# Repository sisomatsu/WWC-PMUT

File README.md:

# WWC-PMUT
Wearable, Wireless, and Compact PMUTs

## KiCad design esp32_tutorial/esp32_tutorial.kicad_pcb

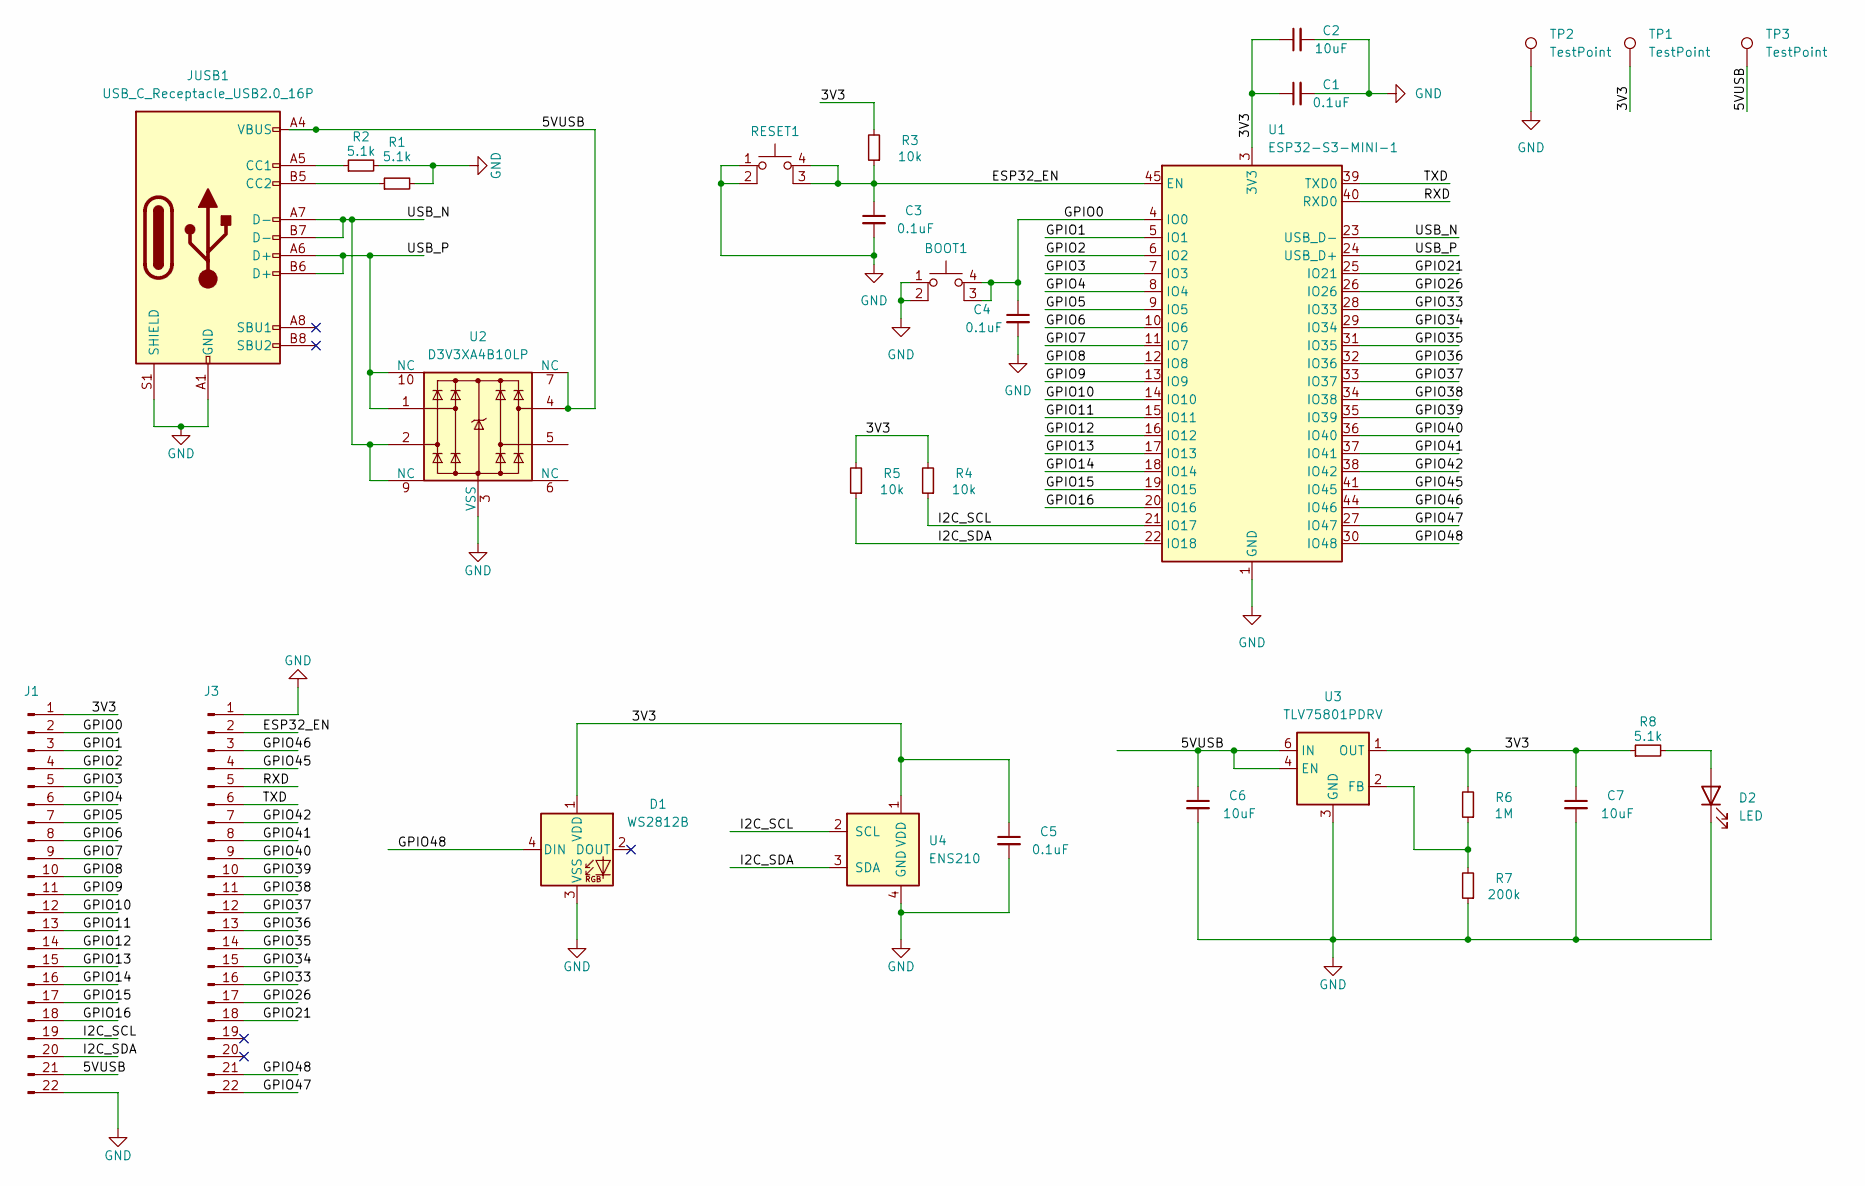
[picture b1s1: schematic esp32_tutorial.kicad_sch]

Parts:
BOOT1: SW_SPST_PTS810
C1, C3, C4, C5: 0.1uF; C_0603_1608Metric
C2, C6, C7: 10uF; C_0603_1608Metric
D1: WS2812B; LED_WS2812B_PLCC4_5.0x5.0mm_P3.2mm
D2: LED; LED_0603_1608Metric
J1, J3: PinHeader_1x22_P2.54mm_Vertical
JUSB1: USB_C_Receptacle_USB2.0_16P; USB_C_Receptacle_GCT_USB4105-xx-A_16P_TopMnt_Horizontal
R1, R2, R8: 5.1k; R_0603_1608Metric
R3, R4, R5: 10k; R_0603_1608Metric
R6: 1M; R_0603_1608Metric
R7: 200k; R_0603_1608Metric
RESET1: SW_SPST_PTS810
TP1, TP2, TP3: TestPoint; TP420X150
U1: ESP32-S3-MINI-1; ESP32-S2-MINI-1
U2: D3V3XA4B10LP; Diodes_UDFN-10_1.0x2.5mm_P0.5mm
U3: TLV75801PDRV; WSON-6-1EP_2x2mm_P0.65mm_EP1x1.6mm
U4: ENS210; AMS_QFN-4-1EP_2x2mm_P0.95mm_EP0.7x1.6mm

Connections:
/3V3: C1.1, C2.1, C5.1, C7.1, D1.1 (VDD), J1.1, R3.2, R4.2, R5.2, R6.2, R8.1, TP1.1, U1.3 (3V3), U3.1 (OUT), U4.1 (VDD)
/5VUSB: C6.1, J1.21, JUSB1.A4 (VBUS), JUSB1.A9 (VBUS), JUSB1.B4 (VBUS), JUSB1.B9 (VBUS), TP3.1, U2.4, U2.7 (NC), U3.4 (EN), U3.6 (IN)
/ESP32_EN: C3.1, J3.2, R3.1, RESET1.3 (K), RESET1.4 (A), U1.45 (EN)
/GPIO0: BOOT1.3 (K), BOOT1.4 (A), C4.1, J1.2, U1.4 (IO0)
/GPIO1: J1.3, U1.5 (IO1)
/GPIO2: J1.4, U1.6 (IO2)
/GPIO3: J1.5, U1.7 (IO3)
/GPIO4: J1.6, U1.8 (IO4)
/GPIO5: J1.7, U1.9 (IO5)
/GPIO6: J1.8, U1.10 (IO6)
/GPIO7: J1.9, U1.11 (IO7)
/GPIO8: J1.10, U1.12 (IO8)
/GPIO9: J1.11, U1.13 (IO9)
/GPIO10: J1.12, U1.14 (IO10)
/GPIO11: J1.13, U1.15 (IO11)
/GPIO12: J1.14, U1.16 (IO12)
/GPIO13: J1.15, U1.17 (IO13)
/GPIO14: J1.16, U1.18 (IO14)
/GPIO15: J1.17, U1.19 (IO15)
/GPIO16: J1.18, U1.20 (IO16)
/GPIO21: J3.18, U1.25 (IO21)
/GPIO26: J3.17, U1.26 (IO26)
/GPIO33: J3.16, U1.28 (IO33)
/GPIO34: J3.15, U1.29 (IO34)
/GPIO35: J3.14, U1.31 (IO35)
/GPIO36: J3.13, U1.32 (IO36)
/GPIO37: J3.12, U1.33 (IO37)
/GPIO38: J3.11, U1.34 (IO38)
/GPIO39: J3.10, U1.35 (IO39)
/GPIO40: J3.9, U1.36 (IO40)
/GPIO41: J3.8, U1.37 (IO41)
/GPIO42: J3.7, U1.38 (IO42)
/GPIO45: J3.4, U1.41 (IO45)
/GPIO46: J3.3, U1.44 (IO46)
/GPIO47: J3.22, U1.27 (IO47)
/GPIO48: D1.4 (DIN), J3.21, U1.30 (IO48)
/I2C_SCL: J1.19, R4.1, U1.21 (IO17), U4.2 (SCL)
/I2C_SDA: J1.20, R5.1, U1.22 (IO18), U4.3 (SDA)
/RXD: J3.5, U1.40 (RXD0)
/TXD: J3.6, U1.39 (TXD0)
/USB_N: JUSB1.A7 (D-), JUSB1.B7 (D-), U1.23 (USB_D-), U2.2, U2.9 (NC)
/USB_P: JUSB1.A6 (D+), JUSB1.B6 (D+), U1.24 (USB_D+), U2.1, U2.10 (NC)
GND: BOOT1.1, BOOT1.2, C1.2, C2.2, C3.2, C4.2, C5.2, C6.2, C7.2, D1.3 (VSS), D2.1 (K), J1.22, J3.1, JUSB1.A1 (GND), JUSB1.A12 (GND), JUSB1.B1 (GND), JUSB1.B12 (GND), JUSB1.S1 (SHIELD), R1.2, R2.2, R7.1, RESET1.1, RESET1.2, TP2.1, U1.1 (GND), U1.2 (GND), U1.42 (GND), U1.43 (GND), U1.46 (GND), U1.47 (GND), U1.48 (GND), U1.49 (GND), U1.50 (GND), U1.51 (GND), U1.52 (GND), U1.53 (GND), U1.54 (GND), U1.55 (GND), U1.56 (GND), U1.57 (GND), U1.58 (GND), U1.59 (GND), U1.60 (GND), U1.61 (GND), U1.62 (GND), U1.63 (GND), U1.64 (GND), U1.65 (GND), U2.3 (VSS), U2.8 (VSS), U3.3 (GND), U3.7 (GND), U4.4 (GND), U4.5 (GND)
unnamed: D2.2 (A), R8.2
unnamed: JUSB1.A5 (CC1), R2.1
unnamed: JUSB1.B5 (CC2), R1.1
unnamed: R6.1, R7.2, U3.2 (FB)

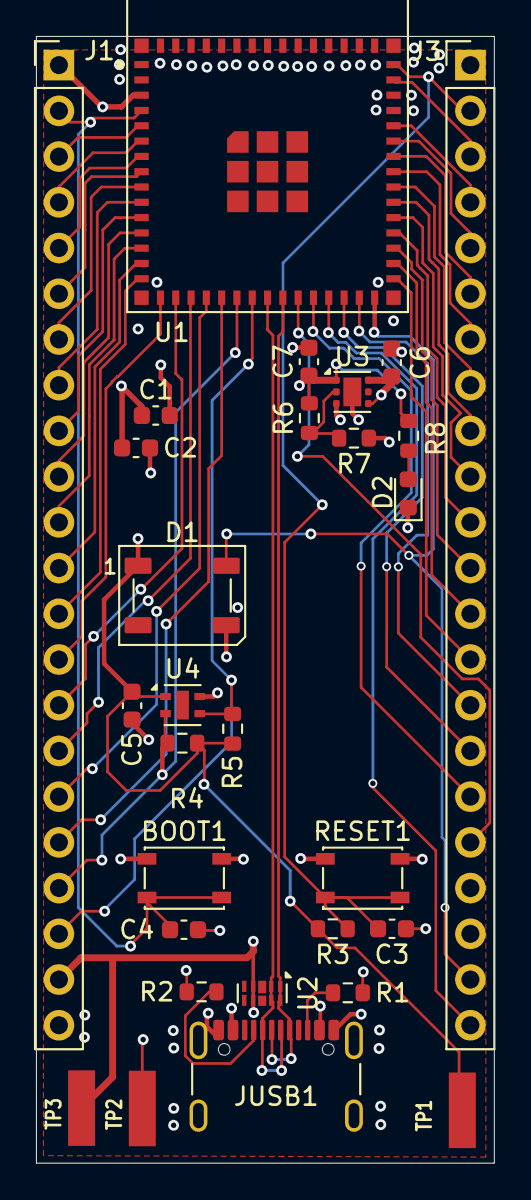
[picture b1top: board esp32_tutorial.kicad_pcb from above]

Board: 4 copper layers, 25.4 x 62.6 mm, 29 parts (0 on the bottom side), 47 nets.

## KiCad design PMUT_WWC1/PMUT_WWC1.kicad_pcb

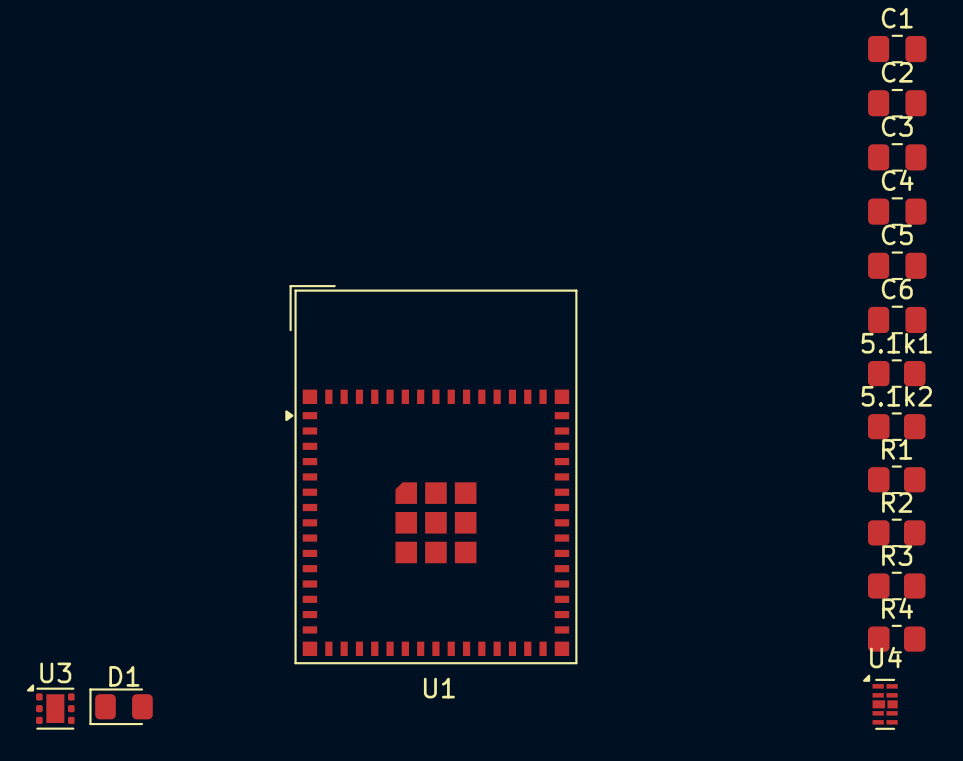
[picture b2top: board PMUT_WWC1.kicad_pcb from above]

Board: 2 copper layers, 16 parts (0 on the bottom side), 9 nets, no tracks yet.

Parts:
5.1k1, 5.1k2: R; R_0805_2012Metric_Pad1.20x1.40mm_HandSolder
C1, C3, C4: 0.1uF; C_0805_2012Metric_Pad1.18x1.45mm_HandSolder
C2, C5, C6: 10uF; C_0805_2012Metric_Pad1.18x1.45mm_HandSolder
D1: LED; D_0805_2012Metric_Pad1.15x1.40mm_HandSolder
R1: 10k; R_0805_2012Metric_Pad1.20x1.40mm_HandSolder
R2: 1M; R_0805_2012Metric_Pad1.20x1.40mm_HandSolder
R3: 200k; R_0805_2012Metric_Pad1.20x1.40mm_HandSolder
R4: 5.1k; R_0805_2012Metric_Pad1.20x1.40mm_HandSolder
U1: ESP32-S3-MINI-1; ESP32-S2-MINI-1
U3: TLV75801PDRV; WSON-6-1EP_2x2mm_P0.65mm_EP1x1.6mm
U4: D3V3XA4B10LP; Diodes_UDFN-10_1.0x2.5mm_P0.5mm

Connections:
/3V3: C1.1, C2.1, C6.1, R1.1, R2.1, R4.1, U1.3 (3V3), U3.1 (OUT)
/5VUSB: C5.1, U3.4 (EN), U3.6 (IN), U4.4, U4.7 (NC)
/GPIO0: C4.1, U1.4 (IO0)
/USB_N: U1.23 (USB_D-), U4.1, U4.10 (NC)
/USB_P: U1.24 (USB_D+), U4.2, U4.9 (NC)
GND: 5.1k1.2, 5.1k2.2, C1.2, C2.2, C3.2, C4.2, C5.2, C6.2, D1.1 (K), R3.2, U1.1 (GND), U1.2 (GND), U1.42 (GND), U1.43 (GND), U1.46 (GND), U1.47 (GND), U1.48 (GND), U1.49 (GND), U1.50 (GND), U1.51 (GND), U1.52 (GND), U1.53 (GND), U1.54 (GND), U1.55 (GND), U1.56 (GND), U1.57 (GND), U1.58 (GND), U1.59 (GND), U1.60 (GND), U1.61 (GND), U1.62 (GND), U1.63 (GND), U1.64 (GND), U1.65 (GND), U3.3 (GND), U3.7 (GND), U4.3 (VSS), U4.8 (VSS)
unnamed: D1.2 (A), R4.2
unnamed: C3.1, R1.2, U1.45 (EN)
unnamed: R2.2, R3.1, U3.2 (FB)

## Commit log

2025-03-19 Add files via upload
    Initial schematic for ESP32 S3 SOLO Module
2025-03-19 Add files via upload
    Initial schematic for ESP32 S3 SOLO with USB C
